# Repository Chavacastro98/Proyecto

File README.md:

# E.L.E.C.T.R.O.D.O-32: Planta Piloto de Electrodeposición y Galvanoplastia
### Equipo de Laboratorio para Experimentación y Control en Tiempo Real con Obtención de Datos Operativos

> [!NOTE]
> **E.L.E.C.T.R.O.D.O-32** es una plataforma ciberfísica de instrumentación y automatización electroquímica desarrollada en la Universidad de Guadalajara (CUCEI). Integra control térmico determinista en tiempo real, generador de corriente constante/pulsada en Celda Hull, supervisión SCADA con culombimetría faradaica y servidores web embebidos.
>
> 🗺️ **Mapa Integral de Arquitectura y Navegación:** [MAPA_DEL_PROYECTO.md](MAPA_DEL_PROYECTO.md)  
> 🌐 **Showcase Técnico Interactivo (GitHub Pages):** [https://chavacastro98.github.io/Proyecto/](https://chavacastro98.github.io/Proyecto/)  
> 🧪 **Manual de Operación Química & Laboratorio:** [documentos/manuales/MANUAL_DE_OPERACION_QUIMICA.html](documentos/manuales/MANUAL_DE_OPERACION_QUIMICA.html) | [En línea en Pages](https://chavacastro98.github.io/Proyecto/manual/)  
> 📑 **Congreso Nacional SMEQ 2026 (Folio CTS-C51):** [eventos/smeq_2026/](eventos/smeq_2026/)  
> 🏆 **InnovaFest 2026 (Expo Guadalajara):** [eventos/innovafest/](eventos/innovafest/)  

---

## 1. De qué trata este sistema

La galvanoplastia sobre aluminio es un proceso notoriamente delicado: el aluminio forma espontáneamente una película pasivante de óxido que arruina la adherencia, mientras que los electrolitos ácidos y las altas corrientes de deposición generan ruido electromagnético y caídas de tensión parásitas que desestabilizan cualquier sensor estándar.

**E.L.E.C.T.R.O.D.O-32** resuelve ese reto construyendo una **planta piloto automatizada de 3 tinas de tratamiento químico + Celda Hull (267 mL)**, gobernada por una arquitectura distribuida donde el hardware, el circuito impreso maestro, el firmware en tiempo real y el software de supervisión en PC trabajan como una sola unidad:

1. **Etapa 1 — Desengrase Alcalino (85-90 °C, 240 s):** Limpieza termoquímica superficial con $\text{Na}_3\text{PO}_4$, $\text{Na}_2\text{SiO}_3$ y PEG-400.
2. **Etapa 2 — Decapado y Activación Alcalina (85-90 °C, 120 s):** Remoción selectiva de la película pasivante de alúmina sin atacar el metal base.
3. **Etapa 3 — Zincado en Celda Hull (25 °C o 40 °C, 120 o 300 s):** Electrodeposición en celda trapezoidal normalizada de 267 mL con corriente continua (1.50 A DC) o pulsada (10 Hz / 20% duty cycle) para evaluar el gradiente de densidad de corriente sobre toda la longitud de la probeta.
4. **Etapa 4 — Niquelado Electrolítico sobre Zinc (30-40 °C, 600 s):** Depósito protector final a 1.13 A DC con baño estabilizado para inhibir el desplazamiento galvánico espontáneo sobre el zinc subyacente.

---

## 2. Arquitectura Técnica (Versión RTOS 2.0)

El sistema opera con la versión de producción **RTOS 2.0**, diseñada para garantizar determinismo temporal, aislamiento total de ruido e instrumentación electroquímica de alta fidelidad:

```mermaid
flowchart TD
    %% CAPA SUPERIOR: RED INALAMBRICA Y SUPERVISION
    SCADA["Estacion SCADA PC (Telemetria 2.0)<br/>Recetas ISA-88, Culombimetria Faraday,<br/>Balanza Analitica y Figuras 300 DPI"]
    WEB["Capa Web Embebida (Core 0)<br/>Web App Movil HTML5 / REST API /data_all (10 Hz)"]

    %% NODO CENTRAL ORQUESTADOR
    ESP["ESP32-S3 Maestro Dual-Core @ 240 MHz<br/>RTOS 2.0 (SMP FreeRTOS)<br/>Core 0: Servidor Web / Core 1: Control Real-Time"]

    %% ENLACE INALÁMBRICO BIDIRECCIONAL (HACIA ARRIBA)
    ESP <.->|"((( Wi-Fi SoftAP 'Uli' 2.4 GHz )))<br/>Telemetria Completa 10 Hz <==> Consignas de Receta"| WEB
    WEB <-->|"Comunicacion Bidireccional HTTP/JSON<br/>Telemetria en Vivo y Comandos de Marcha/Paro"| SCADA

    %% RAMA 1: CONTROL TERMICO AC (EN CASCADA)
    ESP -->|"UART2 TX (9600 bps)<br/>Watchdog 4.0 s"| NANO["Arduino Nano2 (ATmega328P @ 16 MHz)<br/>JELDimmer2 (Ventana 3000 ms + WDT 1s)"]
    NANO -->|"Tiempo Proporcional (3000 ms)<br/>Modulacion por Software"| TRIACS["Modulo 4x TRIACs BTA24-800BW<br/>Optoacopladores MOC3021 (D7 a D10)"]
    TRIACS -->|"Ciclos Completos 60 Hz<br/>Cero Ruido EMI"| CALENTADORES["Calentadores de Inmersion<br/>Tina 1, 2, 4 (450W AC)<br/>Tina 3 - Hull (18W AC)"]

    %% RAMA 2: CORRIENTE GALVANICA VCSS (CORTE BIPOLAR + Y -)
    ESP -->|"Bus I2C (0x60)<br/>Consigna 12-bit (0-3.53V)"| DAC["DAC MCP4725<br/>Reconfigurable Tinas 3 y 4"]
    DAC -->|"Voltaje Analogico Vref"| VCSS["Modulo Sumidero VCSS (Gm = 2.0 S)<br/>OpAmp LM358N + 2x MOSFETs IRLZ44N<br/>Medicion de Corriente en Source (Shunts)"]
    ESP -.->|"GPIO 20 (Active-LOW)<br/>Protocolo ZCS a I=0.00A"| RELE["Modulo Rele 2-Canales (Corte Bipolar)<br/>Aislamiento Fisico Total de Lineas (+) y (-)"]
    RELE <-->|"Corte Bipolar: +12V Anodo y Retorno Catodo"| CELDA["Tinas Electroquimicas Reconfigurables<br/>Tina 3: Celda Hull (Zincado 0-3.50 A)<br/>Tina 4: Niquelado sobre Zinc"]
    CELDA -->|"Retorno de Corriente al Drain"| VCSS
    VCSS -->|"Caida Kelvin en Shunts de Source"| ADS_CURRENT["ADC ADS1115 (Canales A2-A3 Single-Ended)<br/>Telemetria de Corriente I/V (10 Hz)"]
    ADS_CURRENT -->|"Bus I2C Fast-Mode (0x48)"| ESP

    %% RAMA 3: INSTRUMENTACION PH
    ELECTRODO["Electrodo Vidrio BNC + PH-4502C<br/>Acondicionamiento Analogico"] -->|"Senal Diferencial Po vs Ref"| ADS_PH["ADC ADS1115 (Canales A0-A1 Diferencial)<br/>Lectura Pseudo-Diferencial @ 860 SPS"]
    ADS_PH -->|"Bus I2C Fast-Mode (0x48)"| ESP

    %% RAMA 4: TERMOMETRIA
    TERMOS["4x Termopares Industriales Tipo K<br/>(Tinas 1 a 4)"] -->|"Compensacion Union Fria"| MAXS["4x Modulos MAX6675<br/>Digitalizadores SPI 12-bit"]
    MAXS -->|"Bus SPI (SCK=18, MISO=19, 4x CS)"| ESP

    %% RAMA 5: AMBIENTE
    AMB["Sensor Ambiental<br/>AHT20 + BMP280"] -->|"Bus I2C (0x38 / 0x76)"| ESP

    %% ESTILOS VISUALES
    style ESP fill:#0284c7,stroke:#38bdf8,stroke-width:3px,color:#ffffff
    style SCADA fill:#0f172a,stroke:#38bdf8,stroke-width:2px,color:#f8fafc
    style WEB fill:#0369a1,stroke:#38bdf8,stroke-width:2px,color:#ffffff
    style NANO fill:#1e293b,stroke:#f59e0b,stroke-width:2px,color:#f8fafc
    style TRIACS fill:#1e293b,stroke:#f59e0b,stroke-width:1px,color:#f8fafc
    style CALENTADORES fill:#0f172a,stroke:#f59e0b,stroke-width:1px,color:#f8fafc
    style DAC fill:#1e293b,stroke:#8b5cf6,stroke-width:1px,color:#f8fafc
    style VCSS fill:#1e293b,stroke:#8b5cf6,stroke-width:2px,color:#f8fafc
    style RELE fill:#1e293b,stroke:#ec4899,stroke-width:2px,color:#f8fafc
    style CELDA fill:#0f172a,stroke:#8b5cf6,stroke-width:2px,color:#f8fafc
    style ADS_CURRENT fill:#1e293b,stroke:#8b5cf6,stroke-width:2px,color:#f8fafc
    style ELECTRODO fill:#0f172a,stroke:#10b981,stroke-width:1px,color:#f8fafc
    style ADS_PH fill:#1e293b,stroke:#10b981,stroke-width:2px,color:#f8fafc
    style TERMOS fill:#0f172a,stroke:#ef4444,stroke-width:1px,color:#f8fafc
    style MAXS fill:#1e293b,stroke:#ef4444,stroke-width:2px,color:#f8fafc
    style AMB fill:#1e293b,stroke:#06b6d4,stroke-width:2px,color:#f8fafc
```

---

## 3. Sección de Hardware y PCBs: Placa Madre Rev 5.0

La electrónica de control físico ha madurado a un diseño industrial estandarizado en KiCad, disponible en [`hardware/pcb/placa_madre_esp32s3_uno/`](hardware/pcb/placa_madre_esp32s3_uno/):

<p align="center">
  <em>Figura 3.1: Render 3D fotorrealista (Vista Isométrica) de la Placa Madre Industrial Rev 5.0 para ESP32-S3 y Arduino Nano.</em>
</p>

* **Dimensiones y Capas:** $100\text{ mm} \times 100\text{ mm}$, 2 capas en FR-4 TG155, cobre de 1 oz ($35\ \mu\text{m}$) con pistas de potencia ensanchadas (>2.5 mm) y acabado ENIG / HASL con plomo.
* **Aislamiento de Ruido:** Separación física de planos de masa analógica (AGND) e instrumentación digital (DGND), desacoplamiento óptico para los 4 TRIACs (MOC3021 + 4N35) y conmutación en cruce por cero (ZCS a 60 Hz).
* **Entregables de Fabricación:**
  * [Esquemático Electrónico en PDF](hardware/pcb/placa_madre_esp32s3_uno/placa_madre_esp32s3_uno_sch.pdf)
  * [Paquete de Gerbers para JLCPCB (ZIP)](hardware/pcb/placa_madre_esp32s3_uno/GERBERS_PLACA_MADRE_ESP32S3_UNO_REV5.zip)
  * [Lista de Materiales BOM](hardware/pcb/placa_madre_esp32s3_uno/BOM_JLCPCB_ESP32S3_UNO_REV5.csv) y [Coordenadas Pick & Place CPL](hardware/pcb/placa_madre_esp32s3_uno/CPL_JLCPCB_ESP32S3_UNO_REV5.csv)
  * [Modelo 3D CAD STEP](hardware/pcb/placa_madre_esp32s3_uno/placa_madre_esp32s3_uno_3d.step)
  * Renders 3D en Ultra-Alta Definición: [Vista Isométrica](hardware/pcb/placa_madre_esp32s3_uno/render_3d_placa_madre_esp32s3_uno_iso.png) | [Vista Superior](hardware/pcb/placa_madre_esp32s3_uno/render_3d_placa_madre_esp32s3_uno_top.png)

> [!TIP]
> Para la variante de alta velocidad basada en **Arduino UNO Q (Edge Computing)**, consulta el [Carrier Shield Industrial Rev 5.1](../ELECTRODO_32_Uno/hardware/pcb/carrier_shield_uno_q/README.md).

---

## 4. Exposiciones, Congresos y Eventos Tecnológicos

El proyecto cuenta con un espacio dedicado a la divulgación, transferencia tecnológica y memoria científica en [`eventos/`](eventos/):

* **[InnovaFest Guadalajara 2026 (`eventos/innovafest/`)](eventos/innovafest/):**
  * Presentación oficial en **Expo Guadalajara** (23 de Octubre de 2026) en la categoría **Industria 4.0 y Automatización**.
  * Expediente de postulación, [Ficha Técnica Oficial](eventos/innovafest/documentos_oficiales/Ficha_Innovafest_2026_ELECTRODO32.pdf), video pitch ejecutivo y galería de más de 670 registros fotográficos clasificados del prototipo in-operando.
* **[41º Congreso Nacional SMEQ 2026 (`eventos/smeq_2026/`)](eventos/smeq_2026/):**
  * Ponencia formal de investigación: **Folio CTS-C51** (*Optimización de Recubrimientos de Zinc sobre Aluminio 6061 T-6*).
  * [Cartel Científico Oficial en PDF](eventos/smeq_2026/cartel_cientifico/Cartel%20PModular%20044.pptx.pdf) y [Hoja de Mesa con Código QR en PDF](eventos/smeq_2026/cartel_cientifico/HOJA_QR_MESA_SMEQ2026.pdf).
  * [Memoria en Extenso](eventos/smeq_2026/documentos_oficiales/) y reporte final de cinéticas electroquímicas.

---

## 5. Estructura del Repositorio

```
ELECTRODO_32/
├── MAPA_DEL_PROYECTO.md       <- Índice maestro y matriz de navegación técnica
├── Iniciar_Sistema.bat        <- Panel de control unificado por consola
├── Iniciar_Telemetria_2.0.bat <- Lanzador directo del SCADA Telemetría 2.0
├── launcher.py                <- Interfaz gráfica lanzadora en Python
├── MATRIZ_INTERLOCKS.md       <- Enclavamientos y seguridad ISA-84 / SIL-2
│
├── hardware/                  <- Electrónica e ingeniería física
│   ├── pcb/                   <- Circuitos impresos de producción (KiCad, Gerbers, BOM, 3D)
│   │   └── placa_madre_esp32s3_uno/
│   ├── esquemas_electricos/   <- Diagramas de cableado y alambrado de potencia
│   └── control_matlab/        <- Modelos de transferencia de calor y control PI
│
├── eventos/                   <- Hub de exposiciones y congresos
│   ├── innovafest/            <- Postulación, pitch, ficha oficial y galería
│   └── smeq_2026/             <- Cartel Folio CTS-C51, memorias y hoja QR
│
├── software/                  <- Software de estación y supervisión
│   ├── telemetria2.0/         <- SCADA de producción (Tkinter, Faraday, Recetas ISA-88)
│   └── exportar_graficas_offline.py <- Generador de figuras científicas a 300 DPI
│
├── firmware/                  <- Código embebido de tiempo real
│   ├── esp32s3/               <- Firmware ESP32-S3 RTOS 2.0 (FreeRTOS SMP)
│   └── nano2/                 <- Firmware esclavo ATmega328P (JELDimmer2)
│
├── documentos/                <- Manuales y literatura técnica
│   ├── manuales/              <- Manual de Operación Química y Protocolos
│   ├── guias/                 <- Guías de desarrollo y CHANGELOG
│   └── academicos/            <- Protocolos de titulación y referencias
│
├── docs/                      <- Web pública para GitHub Pages (Showcase Web)
└── tests/                     <- Suite automatizada de pruebas (62 passed)
```

---

## 6. Aseguramiento de Calidad y Pruebas Automatizadas

El proyecto cuenta con una suite de **62 pruebas unitarias y de integración** que se ejecutan con `pytest` alcanzando un **95% de cobertura de código**:

```bash
python -m pytest -v
```

* **Física y Metrología ([tests/test_calculos.py](tests/test_calculos.py)):** Verificación matemática de la masa teórica faradaica en DC y pulsado ponderado por ciclo de trabajo, inmunidad de integración en reposo, modelo bicapa aditivo Zn+Ni, espesores micrométricos y linealización de retardo TRIAC de 60 Hz.
* **Interlocks de Seguridad ([tests/test_interlocks.py](tests/test_interlocks.py)):** Verificación del aislamiento entre electrodo de pH y lazo de corriente, enclavamiento por Fail-Safe, restricciones de calibración y conmutación ZCS.
* **Contratos de Telemetría ([tests/test_telemetria_json.py](tests/test_telemetria_json.py)):** Validación de rangos del DAC (0 a 4095), transconductancia Gm, resolución de sensores y manejo defensivo ante pérdidas parciales de paquetes.
* **Consistencia Web ([tests/test_constantes_web.py](tests/test_constantes_web.py)):** Asegura que las constantes de ingeniería del SCADA coincidan con la web pública en `docs/index.html`.

---

## 7. Puesta en Marcha

### Requisitos:
* Sistema operativo Windows 10 u 11.
* Python 3.9 o superior.

### Ejecución:
1. Instalar dependencias:
   ```bash
   pip install -r requirements.txt
   ```
2. Iniciar el Panel Maestro:
   * Doble clic en [`Iniciar_Sistema.bat`](Iniciar_Sistema.bat), o
   * Ejecutar: `python launcher.py`
3. Iniciar directamente el SCADA de Telemetría 2.0:
   * Doble clic en [`Iniciar_Telemetria_2.0.bat`](Iniciar_Telemetria_2.0.bat)

---

## 8. Equipo de Investigación y Desarrollo

### 🧪 Investigación Electroquímica & Tesis de Grado
* **Víctor Ulises Gutiérrez Ramírez** — [victor.gutierrez7221@alumnos.udg.mx](mailto:victor.gutierrez7221@alumnos.udg.mx)  
  * *Investigación electroquímica, formulación de baños, diseño experimental Celda Hull y gravimetría.*

### ⚙️ Automatización, Hardware e Instrumentación (Salvador² C Dev Team)
* **Salvador Castro Pérez** — [salvador.castro7435@alumnos.udg.mx](mailto:salvador.castro7435@alumnos.udg.mx)  
* **Fernando Salvador Samayoa Martínez** — [fernando.samayoa0621@alumnos.udg.mx](mailto:fernando.samayoa0621@alumnos.udg.mx)  

### 🎓 Directores de Tesis
* **Dr. Omar Alejandro González Meza** — Profesor Investigador, CUCEI, Universidad de Guadalajara.
* **Dr. Norberto Casillas Santana** — Profesor Investigador, Departamento de Química, CUCEI, Universidad de Guadalajara.

---

**Salvador² C Dev Team**  
*Centro Universitario de Ciencias Exactas e Ingenierías (CUCEI) — Universidad de Guadalajara.*

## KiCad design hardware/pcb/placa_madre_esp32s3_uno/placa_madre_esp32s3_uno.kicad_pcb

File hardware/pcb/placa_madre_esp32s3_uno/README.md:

# ⚡ Placa Madre Industrial: ESP32-S3 + Arduino Nano (Rev 5.0)
### Módulo Central de Control Ciberfísico, Aislamiento Galvánico y Telemetría

La **Placa Madre Industrial Rev 5.0** es el circuito impreso maestro de **E.L.E.C.T.R.O.D.O-32**, diseñado específicamente para operar en entornos de laboratorio electroquímico con presencia de ruido electromagnético severo (conmutación de TRIACs a 1.37 kW) y corrientes galvánicas continuas o pulsadas de hasta 3.50 A.

---

## 🛠️ 1. Especificaciones de Fabricación (JLCPCB)

| Parámetro | Especificación Técnica | Justificación de Ingeniería |
| :--- | :--- | :--- |
| **Dimensiones** | $100\text{ mm} \times 100\text{ mm}$ (Formato Estándar Económico) | Optimización de costo en panelizado y encaje en gabinete DIN. |
| **Número de Capas** | **2 Capas** (Top: Señales / Bottom: Plano de Tierra Masivo) | Disipación térmica, inmunidad EMI y retorno de baja impedancia. |
| **Material Base** | **FR-4 TG155** (Alta Temperatura) | Resistencia a proximidad de disipadores térmicos de MOSFETs y TRIACs. |
| **Grosor de Placa** | $1.6\text{ mm} \pm 10\%$ | Rigidez mecánica ante inserción de borneras y módulos. |
| **Grosor de Cobre** | **1 oz ($35\ \mu\text{m}$)** externo | Suficiente para pistas de potencia ensanchadas (>2.5 mm con estañado). |
| **Acabado Superficial** | **HASL con plomo** o **ENIG (Electroless Nickel Immersion Gold)** | Excelente soldabilidad y resistencia a la corrosión por vapores ácidos. |
| **Color de Máscara / Serigrafía** | Azul Industrial / Blanco | Contraste de lectura en serigrafía para rotulado de bornes y jumpers. |

---

## 🧩 2. Módulos y Arquitectura Integrada en la Placa

1. **Zócalo para ESP32-S3 DevKitC-1 (44 pines):**
   * Orquestador maestro dual-core a 240 MHz (FreeRTOS SMP).
   * Servidor Web SoftAP "Uli" a 10 Hz + enlaces SPI/I2C/UART aislados.
2. **Zócalo para Arduino Nano (ATmega328P @ 16 MHz):**
   * Coprocesador esclavo de ráfagas para modulación por tiempo proporcional (3000 ms) de los 4 TRIACs.
   * Watchdog por hardware de 1.0 s para fail-safe térmico indestructible.
3. **Sección Analógica e Instrumentación (Aislamiento Faraday):**
   * Zócalo para módulo **ADC ADS1115 (16-bit I2C)**: Canales A0-A1 para pH pseudo-diferencial; Canales A2-A3 para lectura de corriente en shunts Kelvin de bajo ruido.
   * Zócalo para **DAC MCP4725 (12-bit I2C)**: Generador de consigna continua o pulsada ($0\text{--}3.53\text{ V}$) hacia la fuente VCSS.
   * Conector para **Acondicionador de pH PH-4502C** con conector BNC blindado.
   * Zócalos para 4x módulos **MAX6675 SPI** para termopares Tipo K de inmersión.
4. **Sección de Potencia y Seguridad Activa:**
   * Etapa sumidero de corriente constante **VCSS** ($G_m = 2.0\text{ S}$) con 2x MOSFETs de potencia **IRLZ44N** y amplificador operacional **LM358N**.
   * Relé de corte bipolar para aislamiento físico total de ánodo (+) y cátodo (-) con protocolo **Zero-Current Switching (ZCS)**.

---

## 📦 3. Archivos de Fabricación y Producción

* **Esquemático KiCad:** [`placa_madre_esp32s3_uno.kicad_sch`](placa_madre_esp32s3_uno.kicad_sch) | [Esquemático en PDF](placa_madre_esp32s3_uno_sch.pdf)
* **Diseño de PCB KiCad:** [`placa_madre_esp32s3_uno.kicad_pcb`](placa_madre_esp32s3_uno.kicad_pcb)
* **Gerbers Listos para Producción (Rev 5.0):** [`GERBERS_PLACA_MADRE_ESP32S3_UNO_REV5.zip`](GERBERS_PLACA_MADRE_ESP32S3_UNO_REV5.zip)
* **Lista de Materiales JLCPCB (BOM):** [`BOM_JLCPCB_ESP32S3_UNO_REV5.csv`](BOM_JLCPCB_ESP32S3_UNO_REV5.csv)
* **Coordenadas Pick & Place (CPL):** [`CPL_JLCPCB_ESP32S3_UNO_REV5.csv`](CPL_JLCPCB_ESP32S3_UNO_REV5.csv)
* **Modelo 3D CAD Completo:** [`placa_madre_esp32s3_uno_3d.step`](placa_madre_esp32s3_uno_3d.step)
* **Renders Fotorrealistas 3D:**
  * Vista Isométrica: [`render_3d_placa_madre_esp32s3_uno_iso.png`](render_3d_placa_madre_esp32s3_uno_iso.png)
  * Vista Superior (Top): [`render_3d_placa_madre_esp32s3_uno_top.png`](render_3d_placa_madre_esp32s3_uno_top.png)
* **Reporte de Reglas de Diseño (DRC):** [`DRC_REPORT_ESP32S3_UNO.json`](DRC_REPORT_ESP32S3_UNO.json) (0 Violaciones de aislamiento / 0 pistas no conectadas).

---

*Regresar al [Índice de Hardware](../../README.md).*

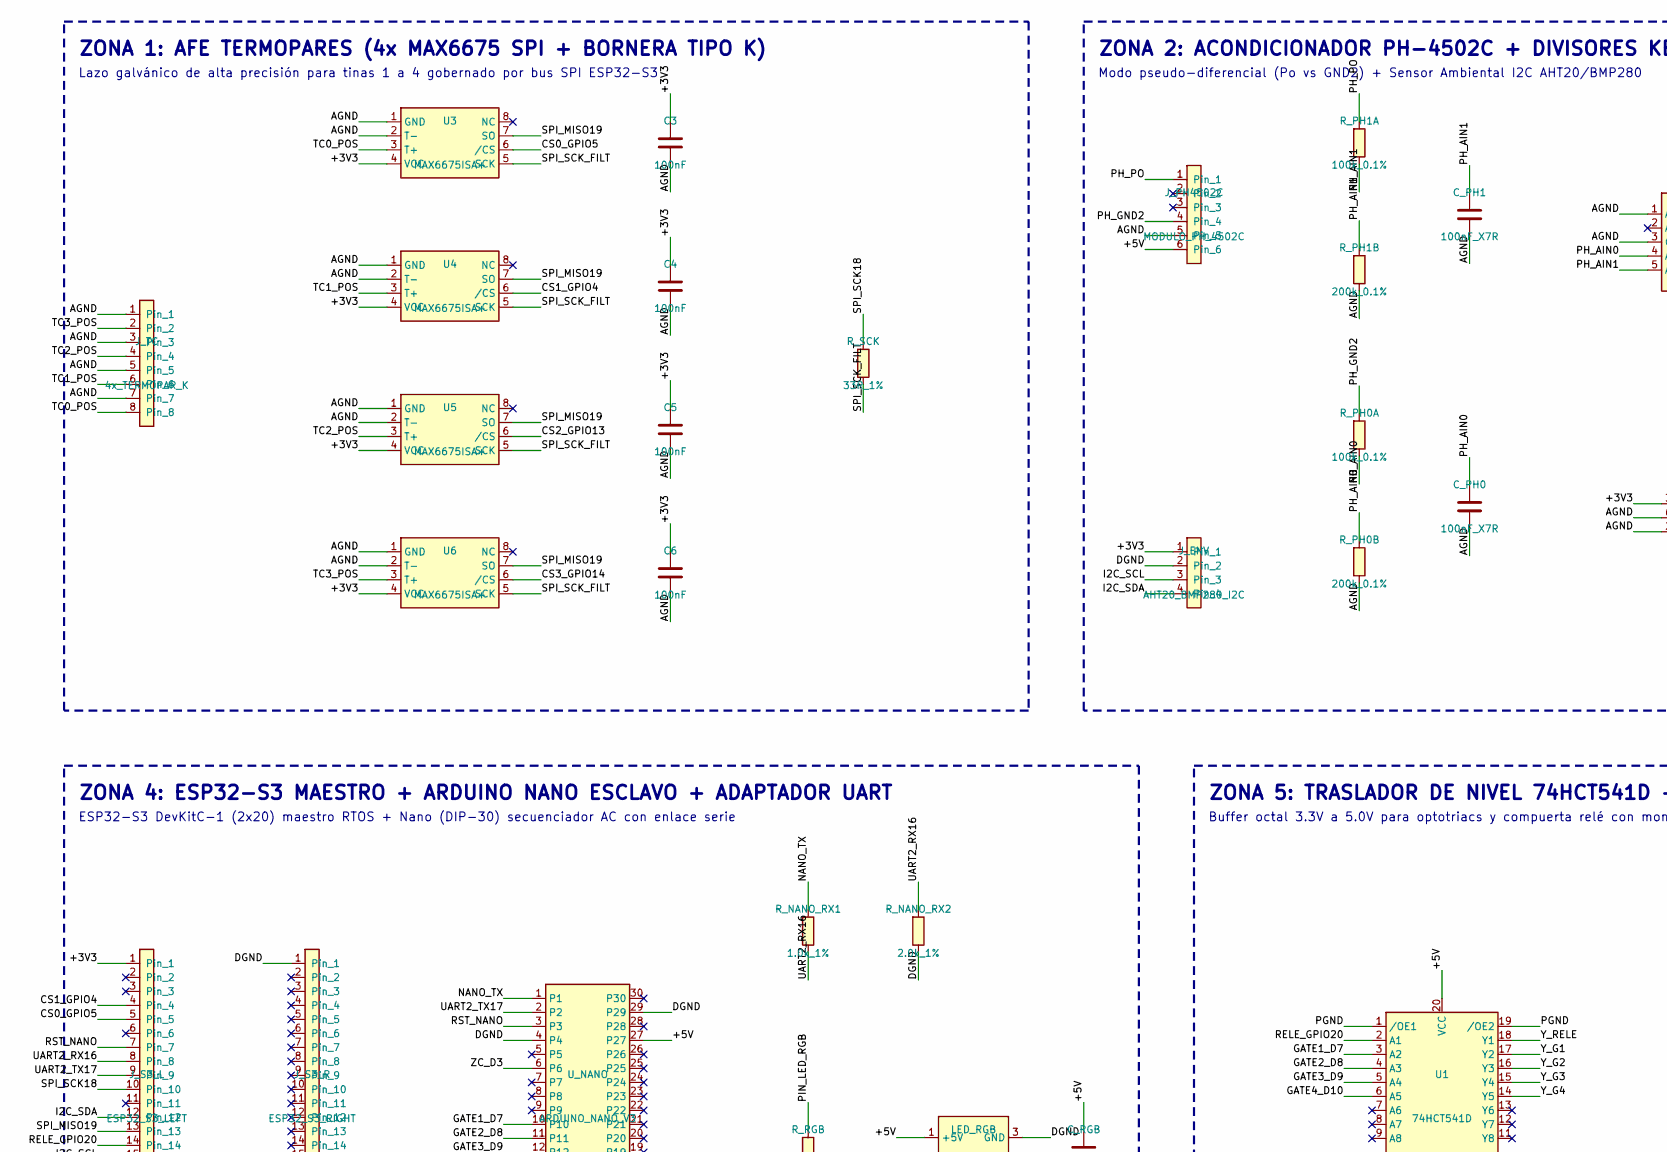
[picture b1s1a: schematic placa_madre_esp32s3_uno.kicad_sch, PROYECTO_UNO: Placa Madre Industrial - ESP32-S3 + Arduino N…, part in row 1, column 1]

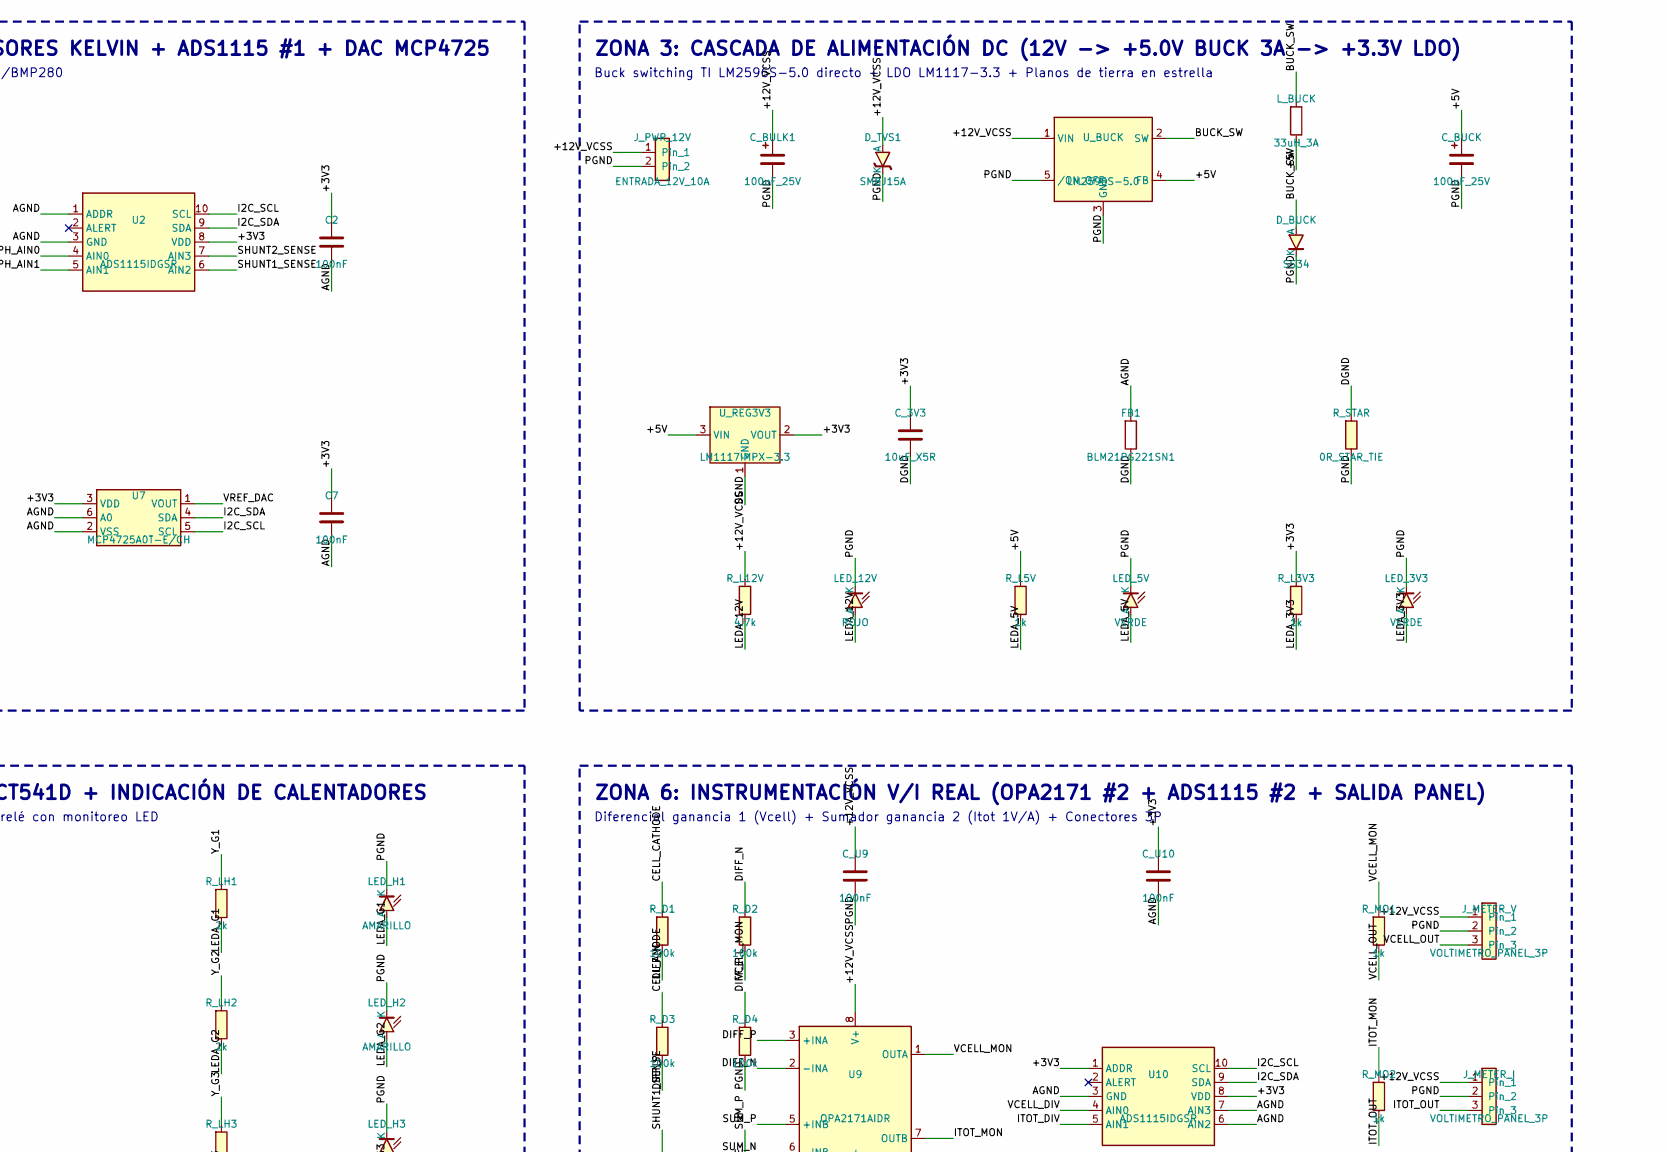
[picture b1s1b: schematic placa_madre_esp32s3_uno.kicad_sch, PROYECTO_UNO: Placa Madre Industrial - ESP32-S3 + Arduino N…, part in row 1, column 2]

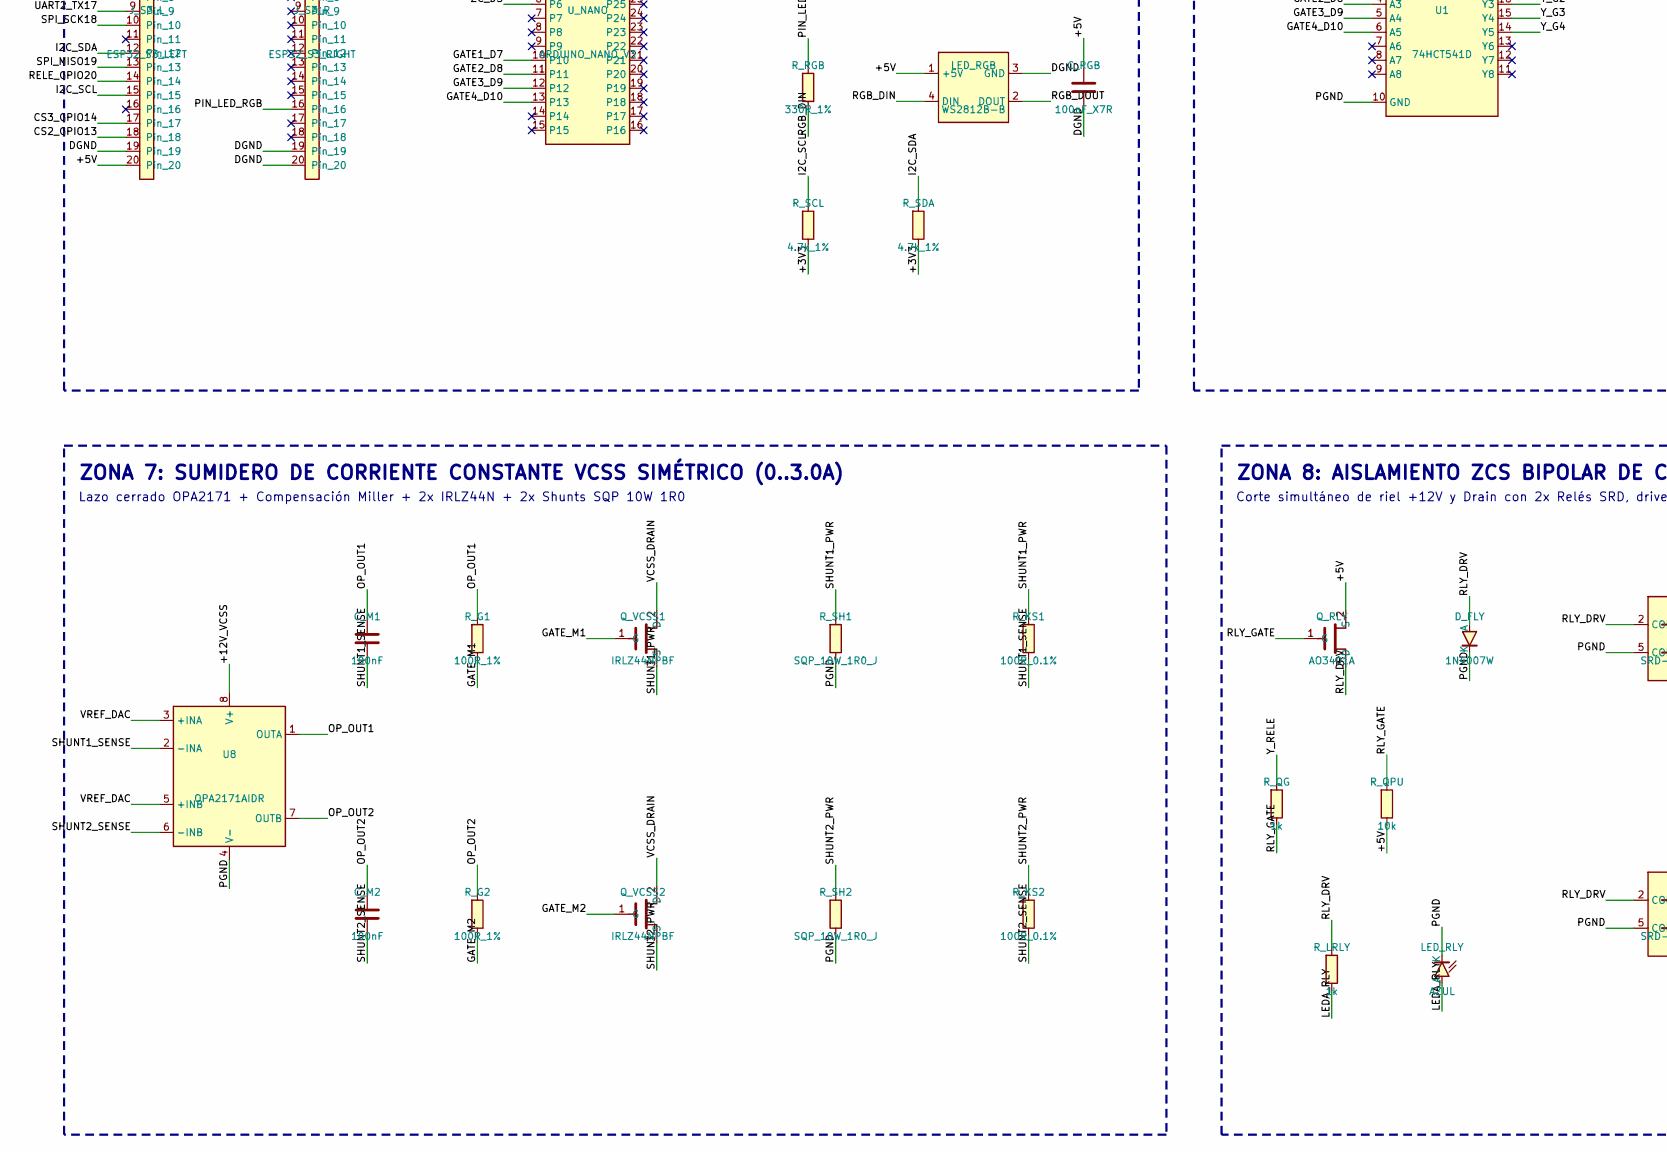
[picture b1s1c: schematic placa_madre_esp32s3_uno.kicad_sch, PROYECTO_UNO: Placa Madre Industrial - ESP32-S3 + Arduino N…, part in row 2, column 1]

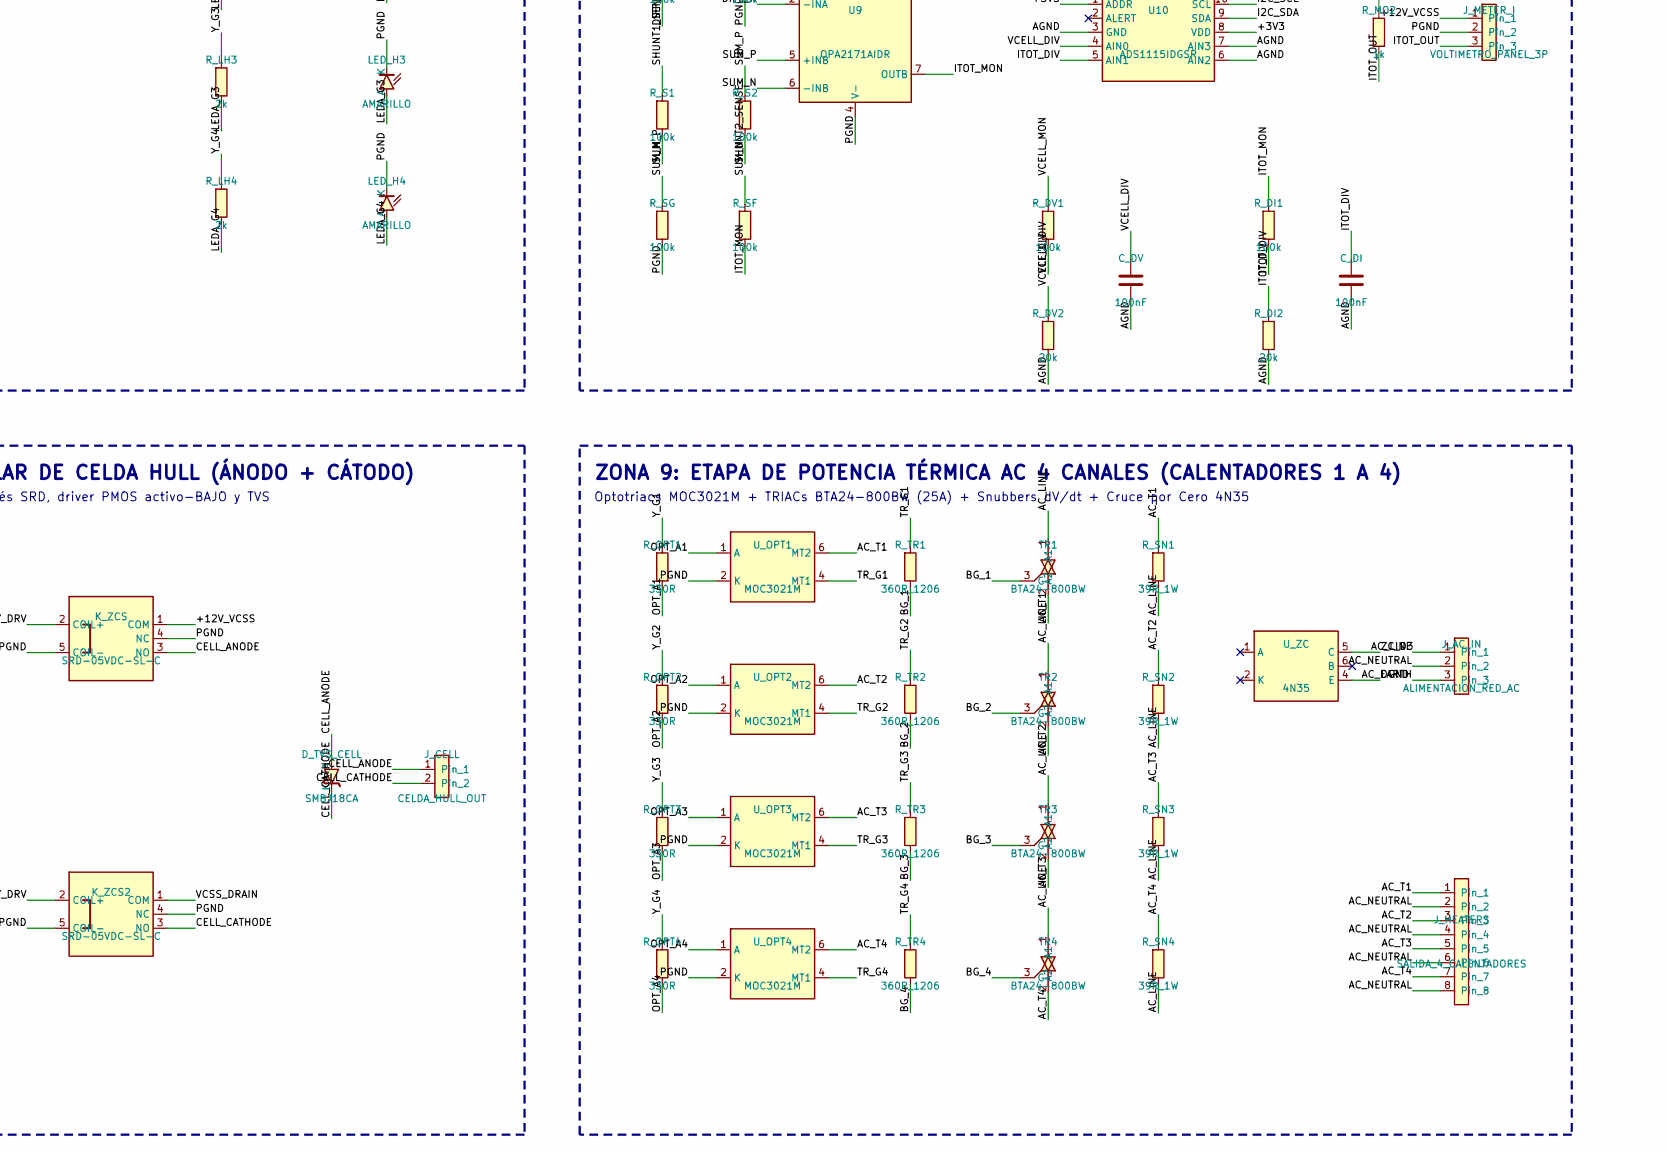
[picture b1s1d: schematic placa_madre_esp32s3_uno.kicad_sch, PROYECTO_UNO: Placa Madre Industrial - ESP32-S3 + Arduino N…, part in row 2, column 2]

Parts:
C2, C3, C4, C5, C6, C7: 100nF; C_0805_2012Metric
C_3V3: 10uF_X5R; C_0805_2012Metric
C_BUCK: 100uF_25V; CP_Elec_6.3x7.7
C_BULK1: 100uF_25V; CP_Elec_6.3x7.7
C_DI: 100nF; C_0805_2012Metric
C_DV: 100nF; C_0805_2012Metric
C_M1, C_M2: 100nF; C_0805_2012Metric
C_PH0, C_PH1: 100nF_X7R; C_0805_2012Metric
C_RGB: 100nF_X7R; C_0805_2012Metric
C_U9, C_U10: 100nF; C_0805_2012Metric
D_BUCK: SS34; D_SMB
D_FLY: 1N4007W; D_SMA
D_TVS1: SMBJ15A; D_SMB
D_TVS_CELL: SMBJ18CA; D_SMB
FB1: BLM21PG221SN1; L_0805_2012Metric
J_AC_IN: ALIMENTACION_RED_AC; TerminalBlock_Phoenix_MKDS-1,5-3-5.08_1x03_P5.08mm_Horizont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
J_CELL: CELDA_HULL_OUT; TerminalBlock_Phoenix_MKDS-1,5-2-5.08_1x02_P5.08mm_Horizont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
J_ENV: AHT20_BMP280_I2C; PinSocket_1x04_P2.54mm_Vertical
J_HEATERS: SALIDA_4_CALENTADORES; TerminalBlock_Phoenix_MKDS-1,5-8-5.08_1x08_P5.08mm_Horizont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
J_METER_I: VOLTIMETRO_PANEL_3P; TerminalBlock_Phoenix_MKDS-1,5-3-5.08_1x03_P5.08mm_Horizont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
J_METER_V: VOLTIMETRO_PANEL_3P; TerminalBlock_Phoenix_MKDS-1,5-3-5.08_1x03_P5.08mm_Horizont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
J_PH4502C: MODULO_PH_4502C; PinSocket_1x06_P2.54mm_Vertical
J_PWR_12V: ENTRADA_12V_10A; TerminalBlock_Phoenix_MKDS-1,5-2-5.08_1x02_P5.08mm_Horizont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
J_S3_L: ESP32_S3_LEFT; PinSocket_1x20_P2.54mm_Vertical
J_S3_R: ESP32_S3_RIGHT; PinSocket_1x20_P2.54mm_Vertical
J_TC: 4x_TERMOPAR_K; TerminalBlock_Phoenix_MKDS-1,5-8-5.08_1x08_P5.08mm_Horizont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
K_ZCS, K_ZCS2: SRD-05VDC-SL-C; Relay_SPDT_SANYOU_SRD_Series_Form_C
LED_3V3, LED_5V: VERDE; LED_0805_2012Metric
LED_12V: ROJO; LED_0805_2012Metric
LED_H1, LED_H2, LED_H3, LED_H4: AMARILLO; LED_0805_2012Metric
LED_RGB: WS2812B-B; LED_WS2812B_PLCC4_5.0x5.0mm_P3.2mm
LED_RLY: AZUL; LED_0805_2012Metric
L_BUCK: 33uH_3A; L_Bourns_SRR1260
Q_RLY: AO3401A; SOT-23
Q_VCSS1, Q_VCSS2: IRLZ44NPBF; TO-220-3_Vertical
R_D1, R_D2, R_D3, R_D4: 100k; R_0805_2012Metric
R_DI1: 100k; R_0805_2012Metric
R_DI2: 20k; R_0805_2012Metric
R_DV1: 100k; R_0805_2012Metric
R_DV2: 20k; R_0805_2012Metric
R_G1, R_G2: 100R_1%; R_0805_2012Metric
R_KS1, R_KS2: 100R_0.1%; R_0805_2012Metric
R_L3V3, R_L5V: 1k; R_0805_2012Metric
R_L12V: 4.7k; R_0805_2012Metric
R_LH1, R_LH2, R_LH3, R_LH4: 2k; R_0805_2012Metric
R_LRLY: 1k; R_0805_2012Metric
R_MO1, R_MO2: 1k; R_0805_2012Metric
R_NANO_RX1: 1.0k_1%; R_0805_2012Metric
R_NANO_RX2: 2.0k_1%; R_0805_2012Metric
R_OPT1, R_OPT2, R_OPT3, R_OPT4: 330R; R_0805_2012Metric
R_PH0A, R_PH1A: 100k_0.1%; R_0805_2012Metric
R_PH0B, R_PH1B: 200k_0.1%; R_0805_2012Metric
R_QG: 1k; R_0805_2012Metric
R_QPU: 10k; R_0805_2012Metric
R_RGB: 330R_1%; R_0805_2012Metric
R_S1, R_S2: 100k; R_0805_2012Metric
R_SCK: 33R_1%; R_0805_2012Metric
R_SCL: 4.7k_1%; R_0805_2012Metric
R_SDA: 4.7k_1%; R_0805_2012Metric
R_SF: 100k; R_0805_2012Metric
R_SG: 100k; R_0805_2012Metric
R_SH1, R_SH2: SQP_10W_1R0_J; R_Axial_Power_L50.0mm_W9.0mm_P55.88mm
R_SN1, R_SN2, R_SN3, R_SN4: 39R_1W; R_2512_6332Metric
R_STAR: 0R_STAR_TIE; R_0805_2012Metric
R_TR1, R_TR2, R_TR3, R_TR4: 360R_1206; R_1206_3216Metric
TR1, TR2, TR3, TR4: BTA24-800BW; TO-220-3_Vertical
U1: 74HCT541D; SOIC-20W_7.5x12.8mm_P1.27mm
U2, U10: ADS1115IDGSR; MSOP-10_3x3mm_P0.5mm
U3, U4, U5, U6: MAX6675ISA+; SOIC-8_3.9x4.9mm_P1.27mm
U7: MCP4725A0T-E/CH; SOT-23-6
U8, U9: OPA2171AIDR; SOIC-8_3.9x4.9mm_P1.27mm
U_BUCK: LM2596S-5.0; TO-263-5_TabPin3
U_NANO: ARDUINO_NANO_V3; Arduino_Nano
U_OPT1, U_OPT2, U_OPT3, U_OPT4: MOC3021M; DIP-6_W7.62mm
U_REG3V3: LM1117IMPX-3.3; SOT-223-3_TabPin2
U_ZC: 4N35; DIP-6_W7.62mm

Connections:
+3V3: C2.1, C3.1, C4.1, C5.1, C6.1, C7.1, C_3V3.1, C_U10.1, J_ENV.1, J_S3_L.1, R_L3V3.1, R_SCL.2, R_SDA.2, U2.8 (VDD), U3.4 (VCC), U4.4 (VCC), U5.4 (VCC), U6.4 (VCC), U7.3 (VDD), U10.1 (ADDR), U10.8 (VDD), U_REG3V3.2 (VOUT)
+5V: C_BUCK.1, C_RGB.1, J_PH4502C.6, J_S3_L.20, LED_RGB.1 (+5V), L_BUCK.2, Q_RLY.2 (S), R_L5V.1, R_QPU.2, U1.20 (VCC), U_BUCK.4 (FB), U_NANO.27, U_REG3V3.3 (VIN)
+12V_VCSS: C_BULK1.1, C_U9.1, D_TVS1.1 (A), J_METER_I.1, J_METER_V.1, J_PWR_12V.1, K_ZCS.1 (COM), R_L12V.1, U8.8 (V+), U9.8 (V+), U_BUCK.1 (VIN)
AC_EARTH: J_AC_IN.3
AC_LINE: J_AC_IN.1, R_SN1.2, R_SN2.2, R_SN3.2, R_SN4.2, TR1.1 (A1), TR2.1 (A1), TR3.1 (A1), TR4.1 (A1)
AC_NEUTRAL: J_AC_IN.2, J_HEATERS.2, J_HEATERS.4, J_HEATERS.6, J_HEATERS.8
AC_T1: J_HEATERS.1, R_SN1.1, TR1.2 (A2), U_OPT1.6 (MT2)
AC_T2: J_HEATERS.3, R_SN2.1, TR2.2 (A2), U_OPT2.6 (MT2)
AC_T3: J_HEATERS.5, R_SN3.1, TR3.2 (A2), U_OPT3.6 (MT2)
AC_T4: J_HEATERS.7, R_SN4.1, TR4.2 (A2), U_OPT4.6 (MT2)
AGND: C2.2, C3.2, C4.2, C5.2, C6.2, C7.2, C_DI.2, C_DV.2, C_PH0.2, C_PH1.2, C_U10.2, FB1.1, J_PH4502C.5, J_TC.1, J_TC.3, J_TC.5, J_TC.7, R_DI2.2, R_DV2.2, R_PH0B.2, R_PH1B.2, U2.1 (ADDR), U2.3 (GND), U3.1 (GND), U3.2 (T-), U4.1 (GND), U4.2 (T-), U5.1 (GND), U5.2 (T-), U6.1 (GND), U6.2 (T-), U7.2 (VSS), U7.6 (A0), U10.3 (GND), U10.6 (AIN2), U10.7 (AIN3)
BG_1: R_TR1.2, TR1.3 (G)
BG_2: R_TR2.2, TR2.3 (G)
BG_3: R_TR3.2, TR3.3 (G)
BG_4: R_TR4.2, TR4.3 (G)
BUCK_SW: D_BUCK.1 (A), L_BUCK.1, U_BUCK.2 (SW)
CELL_ANODE: D_TVS_CELL.1 (A), J_CELL.1, K_ZCS.3 (NO), R_D3.1
CELL_CATHODE: D_TVS_CELL.2 (K), J_CELL.2, K_ZCS2.3 (NO), R_D1.1
CS0_GPIO5: J_S3_L.5, U3.6 (/CS)
CS1_GPIO4: J_S3_L.4, U4.6 (/CS)
CS2_GPIO13: J_S3_L.18, U5.6 (/CS)
CS3_GPIO14: J_S3_L.17, U6.6 (/CS)
DGND: C_3V3.2, C_RGB.2, FB1.2, J_ENV.2, J_S3_L.19, J_S3_R.1, J_S3_R.19, J_S3_R.20, LED_RGB.3 (GND), R_NANO_RX2.2, R_STAR.1, U_NANO.4, U_NANO.29, U_REG3V3.1 (GND), U_ZC.4 (E)
DIFF_N: R_D1.2, R_D2.1, U9.2 (-INA)
DIFF_P: R_D3.2, R_D4.1, U9.3 (+INA)
GATE1_D7: U1.3 (A2), U_NANO.10
GATE2_D8: U1.4 (A3), U_NANO.11
GATE3_D9: U1.5 (A4), U_NANO.12
GATE4_D10: U1.6 (A5), U_NANO.13
GATE_M1: Q_VCSS1.1 (G), R_G1.2
GATE_M2: Q_VCSS2.1 (G), R_G2.2
I2C_SCL: J_ENV.3, J_S3_L.15, R_SCL.1, U2.10 (SCL), U7.5 (SCL), U10.10 (SCL)
I2C_SDA: J_ENV.4, J_S3_L.12, R_SDA.1, U2.9 (SDA), U7.4 (SDA), U10.9 (SDA)
ITOT_DIV: C_DI.1, R_DI1.2, R_DI2.1, U10.5 (AIN1)
ITOT_MON: R_DI1.1, R_MO2.1, R_SF.2, U9.7 (OUTB)
ITOT_OUT: J_METER_I.3, R_MO2.2
LEDA_3V3: LED_3V3.2 (A), R_L3V3.2
LEDA_5V: LED_5V.2 (A), R_L5V.2
LEDA_12V: LED_12V.2 (A), R_L12V.2
LEDA_G1: LED_H1.2 (A), R_LH1.2
LEDA_G2: LED_H2.2 (A), R_LH2.2
LEDA_G3: LED_H3.2 (A), R_LH3.2
LEDA_G4: LED_H4.2 (A), R_LH4.2
LEDA_RLY: LED_RLY.2 (A), R_LRLY.2
NANO_TX: R_NANO_RX1.1, U_NANO.1
OPT_A1: R_OPT1.2, U_OPT1.1 (A)
OPT_A2: R_OPT2.2, U_OPT2.1 (A)
OPT_A3: R_OPT3.2, U_OPT3.1 (A)
OPT_A4: R_OPT4.2, U_OPT4.1 (A)
OP_OUT1: C_M1.1, R_G1.1, U8.1 (OUTA)
OP_OUT2: C_M2.1, R_G2.1, U8.7 (OUTB)
PGND: C_BUCK.2, C_BULK1.2, C_U9.2, D_BUCK.2 (K), D_FLY.2 (K), D_TVS1.2 (K), J_METER_I.2, J_METER_V.2, J_PWR_12V.2, K_ZCS.4 (NC), K_ZCS.5 (COIL-), K_ZCS2.4 (NC), K_ZCS2.5 (COIL-), LED_3V3.1 (K), LED_5V.1 (K), LED_12V.1 (K), LED_H1.1 (K), LED_H2.1 (K), LED_H3.1 (K), LED_H4.1 (K), LED_RLY.1 (K), R_D4.2, R_SG.2, R_SH1.2, R_SH2.2, R_STAR.2, U1.1 (/OE1), U1.10 (GND), U1.19 (/OE2), U8.4 (V-), U9.4 (V-), U_BUCK.3 (GND), U_BUCK.5 (/ON_OFF), U_OPT1.2 (K), U_OPT2.2 (K), U_OPT3.2 (K), U_OPT4.2 (K)
PH_AIN0: C_PH0.1, R_PH0A.2, R_PH0B.1, U2.4 (AIN0)
PH_AIN1: C_PH1.1, R_PH1A.2, R_PH1B.1, U2.5 (AIN1)
PH_GND2: J_PH4502C.4, R_PH0A.1
PH_PO: J_PH4502C.1, J_PH4502C.3, R_PH1A.1
PIN_LED_RGB: J_S3_R.16, R_RGB.1
RELE_GPIO20: J_S3_L.14, U1.2 (A1)
RGB_DIN: LED_RGB.4 (DIN), R_RGB.2
RGB_DOUT: LED_RGB.2 (DOUT)
RLY_DRV: D_FLY.1 (A), K_ZCS.2 (COIL+), K_ZCS2.2 (COIL+), Q_RLY.3 (D), R_LRLY.1
RLY_GATE: Q_RLY.1 (G), R_QG.2, R_QPU.1
RST_NANO: J_S3_L.7, U_NANO.3
SHUNT1_PWR: Q_VCSS1.3 (S), R_KS1.1, R_SH1.1
SHUNT1_SENSE: C_M1.2, R_KS1.2, R_S1.1, U2.6 (AIN2), U8.2 (-INA)
SHUNT2_PWR: Q_VCSS2.3 (S), R_KS2.1, R_SH2.1
SHUNT2_SENSE: C_M2.2, R_KS2.2, R_S2.2, U2.7 (AIN3), U8.6 (-INB)
SPI_MISO19: J_S3_L.13, U3.7 (SO), U4.7 (SO), U5.7 (SO), U6.7 (SO)
SPI_SCK18: J_S3_L.10, R_SCK.1
SPI_SCK_FILT: R_SCK.2, U3.5 (SCK), U4.5 (SCK), U5.5 (SCK), U6.5 (SCK)
SUM_N: R_SF.1, R_SG.1, U9.6 (-INB)
SUM_P: R_S1.2, R_S2.1, U9.5 (+INB)
TC0_POS: J_TC.8, U3.3 (T+)
TC1_POS: J_TC.6, U4.3 (T+)
TC2_POS: J_TC.4, U5.3 (T+)
TC3_POS: J_TC.2, U6.3 (T+)
TR_G1: R_TR1.1, U_OPT1.4 (MT1)
TR_G2: R_TR2.1, U_OPT2.4 (MT1)
TR_G3: R_TR3.1, U_OPT3.4 (MT1)
TR_G4: R_TR4.1, U_OPT4.4 (MT1)
UART2_RX16: J_S3_L.8, R_NANO_RX1.2, R_NANO_RX2.1
UART2_TX17: J_S3_L.9, U_NANO.2
VCELL_DIV: C_DV.1, R_DV1.2, R_DV2.1, U10.4 (AIN0)
VCELL_MON: R_D2.2, R_DV1.1, R_MO1.1, U9.1 (OUTA)
VCELL_OUT: J_METER_V.3, R_MO1.2
VCSS_DRAIN: K_ZCS2.1 (COM), Q_VCSS1.2 (D), Q_VCSS2.2 (D)
VREF_DAC: U7.1 (VOUT), U8.3 (+INA), U8.5 (+INB)
Y_G1: R_LH1.1, R_OPT1.1, U1.17 (Y2)
Y_G2: R_LH2.1, R_OPT2.1, U1.16 (Y3)
Y_G3: R_LH3.1, R_OPT3.1, U1.15 (Y4)
Y_G4: R_LH4.1, R_OPT4.1, U1.14 (Y5)
Y_RELE: R_QG.1, U1.18 (Y1)
ZC_D3: U_NANO.6, U_ZC.5 (C)

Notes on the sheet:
ZONA 1: AFE TERMOPARES (4x MAX6675 SPI + BORNERA TIPO K)
Lazo galvánico de alta precisión para tinas 1 a 4 gobernado por bus SPI ESP32-S3
ZONA 2: ACONDICIONADOR PH-4502C + DIVISORES KELVIN + ADS1115 #1 + DAC MCP4725
Modo pseudo-diferencial (Po vs GND2) + Sensor Ambiental I2C AHT20/BMP280
ZONA 3: CASCADA DE ALIMENTACIÓN DC (12V -> +5.0V BUCK 3A -> +3.3V LDO)
Buck switching TI LM2596S-5.0 directo + LDO LM1117-3.3 + Planos de tierra en estrella
ZONA 4: ESP32-S3 MAESTRO + ARDUINO NANO ESCLAVO + ADAPTADOR UART
ESP32-S3 DevKitC-1 (2x20) maestro RTOS + Nano (DIP-30) secuenciador AC con enlace serie
ZONA 5: TRASLADOR DE NIVEL 74HCT541D + INDICACIÓN DE CALENTADORES
Buffer octal 3.3V a 5.0V para optotriacs y compuerta relé con monitoreo LED
ZONA 6: INSTRUMENTACIÓN V/I REAL (OPA2171 #2 + ADS1115 #2 + SALIDA PANEL)
Diferencial ganancia 1 (Vcell) + Sumador ganancia 2 (Itot 1V/A) + Conectores 3P
ZONA 7: SUMIDERO DE CORRIENTE CONSTANTE VCSS SIMÉTRICO (0..3.0A)
Lazo cerrado OPA2171 + Compensación Miller + 2x IRLZ44N + 2x Shunts SQP 10W 1R0
ZONA 8: AISLAMIENTO ZCS BIPOLAR DE CELDA HULL (ÁNODO + CÁTODO)
Corte simultáneo de riel +12V y Drain con 2x Relés SRD, driver PMOS activo-BAJO y TVS
ZONA 9: ETAPA DE POTENCIA TÉRMICA AC 4 CANALES (CALENTADORES 1 A 4)
Optotriacs MOC3021M + TRIACs BTA24-800BW (25A) + Snubbers dV/dt + Cruce por Cero 4N35

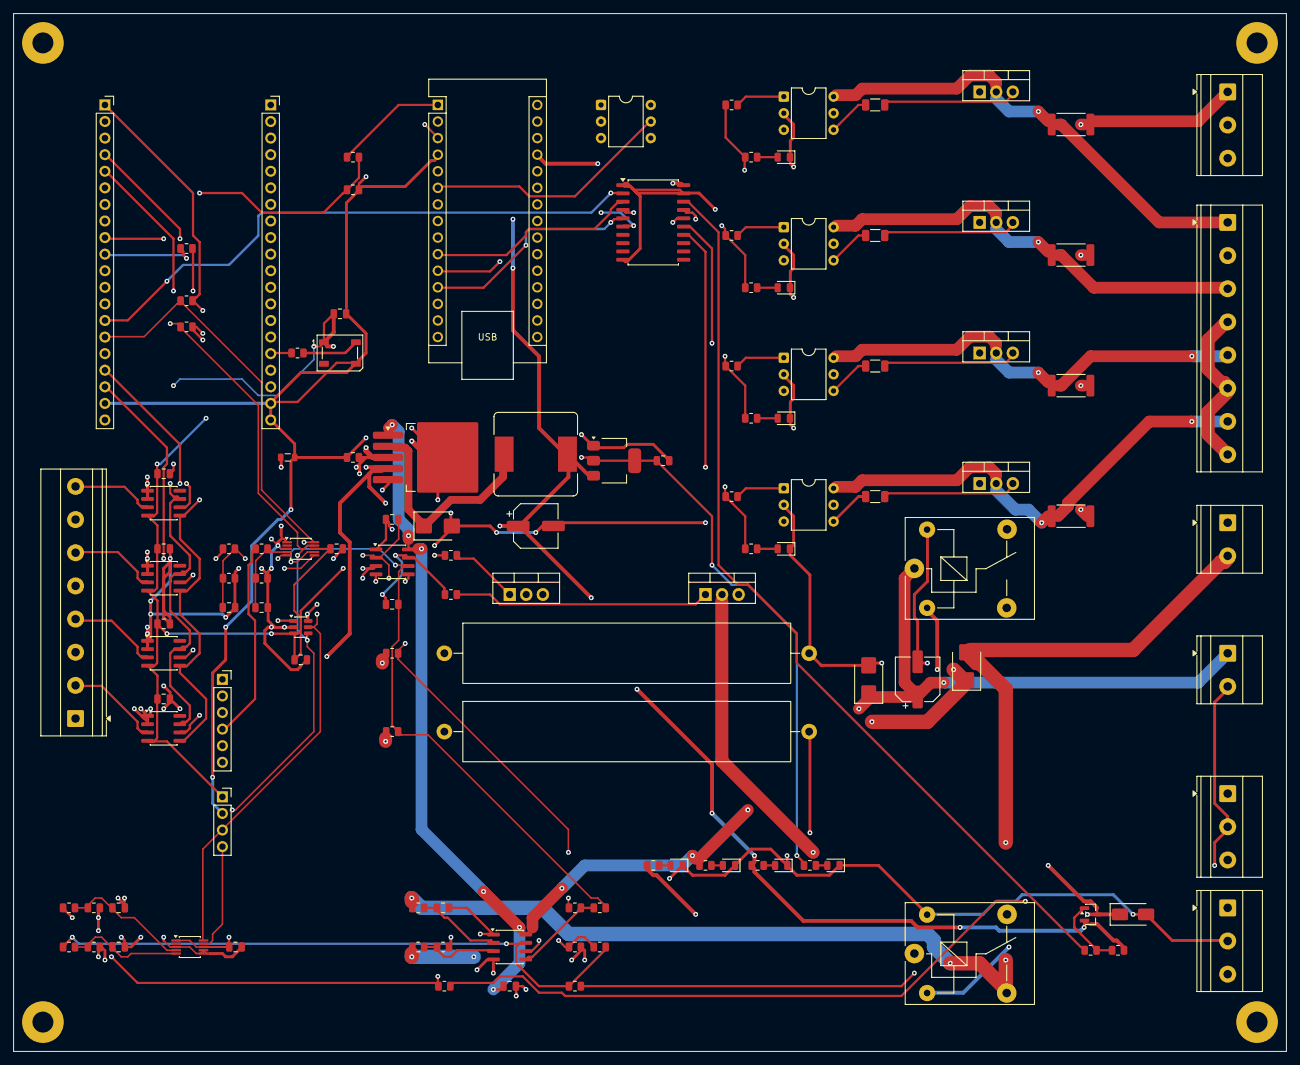
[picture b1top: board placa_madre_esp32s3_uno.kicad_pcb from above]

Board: 4 copper layers, 195.0 x 159.0 mm, 128 parts (0 on the bottom side), 91 nets.

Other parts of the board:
MH1, MH2, MH3, MH4: M3_DIN; MountingHole_3.2mm_M3_Pad

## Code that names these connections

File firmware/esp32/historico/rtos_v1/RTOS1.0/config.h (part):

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 *   4. BMP280  (Dirección 0x76/0x77): Sensor ambiental de presión barométrica.
 * - Sincronización: Cualquier transacción debe estar envuelta en takeI2CMutex() / giveI2CMutex().
 */
#define PIN_I2C_SDA         8   // Bus I2C Datos (SDA)
#define PIN_I2C_SCL         9   // Bus I2C Reloj (SCL)

/**
 * BUS SPI COMPARTIDO (MAX6675 - Termopares Tipo K):
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 * - Indicador de estado de proceso en tiempo real gestionado por Task_Supervisor en Core 1 @ 50 Hz.
 * - Utiliza el LED WS2812 direccionable integrado en la placa ESP32-S3 (GPIO 48 por defecto).
 */
#ifndef PIN_LED_RGB
  #if defined(RGB_BUILTIN)
    #define PIN_LED_RGB     RGB_BUILTIN
  #else
    #define PIN_LED_RGB     48  // Pin de datos WS2812 RGB en ESP32-S3 DevKit
  #endif
#endif

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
